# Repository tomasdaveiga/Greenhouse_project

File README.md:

# Greenhouse_project

Project to collect data (temperature, relative humidity, light) from greenhouse for optimised vegetable growth! The long term goal is to have an autonomous and off-the-grid IoT system with a mobile app for data visualisation and monitoring. 

## Phases

The project is split into different phases:
- ~~Phase 1: Design PCBs and cases for the hardware.~~
- Phase 2: Read data from sensors and show it on a display.
- Phase 3: Integrate wireless data transmission and cloud storage followed by an iOS app for data visualisation.
- Phase 4: Add solar pannels for battery charging.

## Hardware

### Sensors:

- Si7020: Temperature and relative humidity sensor
- OPT3001: Visible light sensor
- *Optional Accelerometer: The greenhouse has a window which opens when the temperature is too high. An accelerometer mounted on the window can tell us if the window is open or shut.*

### Microcontroler:
- PSoC-5LP
- Wifi Module for wireless data transmission.
- LCD Display

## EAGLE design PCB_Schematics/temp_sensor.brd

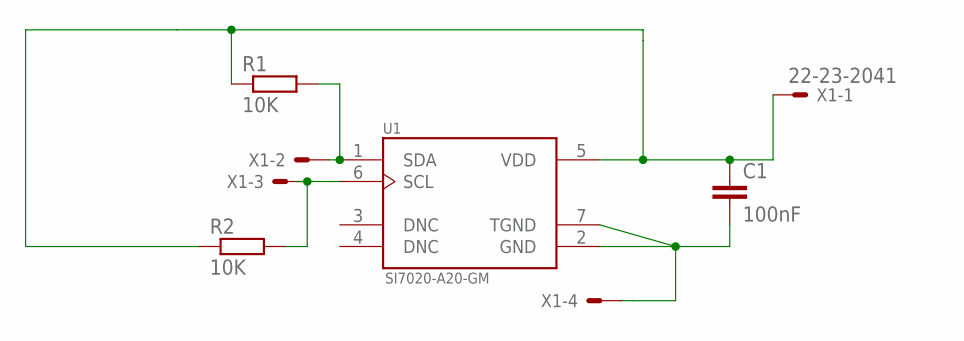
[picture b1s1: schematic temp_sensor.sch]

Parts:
C1: 100nF; C0603
R1, R2: 10K; R0402
U1: SI7020-A20-GM; SON100P300X300X80-7N
X1: 22-23-2041

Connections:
GND: C1.2, U1.2 (GND), U1.7 (TGND), X1.4
SCL: R2.2, U1.6 (SCL), X1.3
SDA: R1.2, U1.1 (SDA), X1.2
VDD: C1.1, R1.1, R2.1, U1.5 (VDD), X1.1

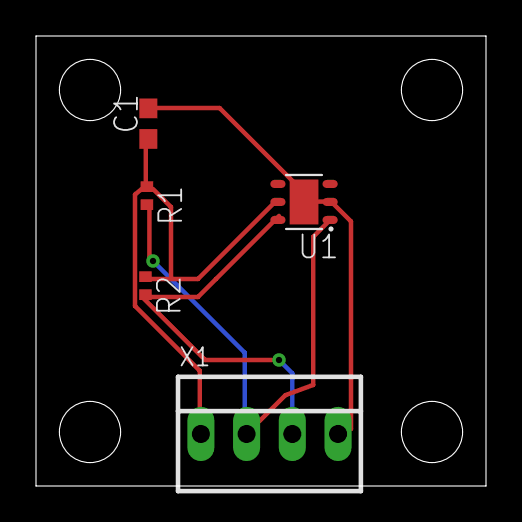
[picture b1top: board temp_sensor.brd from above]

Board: 2 copper layers, 25.0 x 25.0 mm, 5 parts (0 on the bottom side), 4 nets.

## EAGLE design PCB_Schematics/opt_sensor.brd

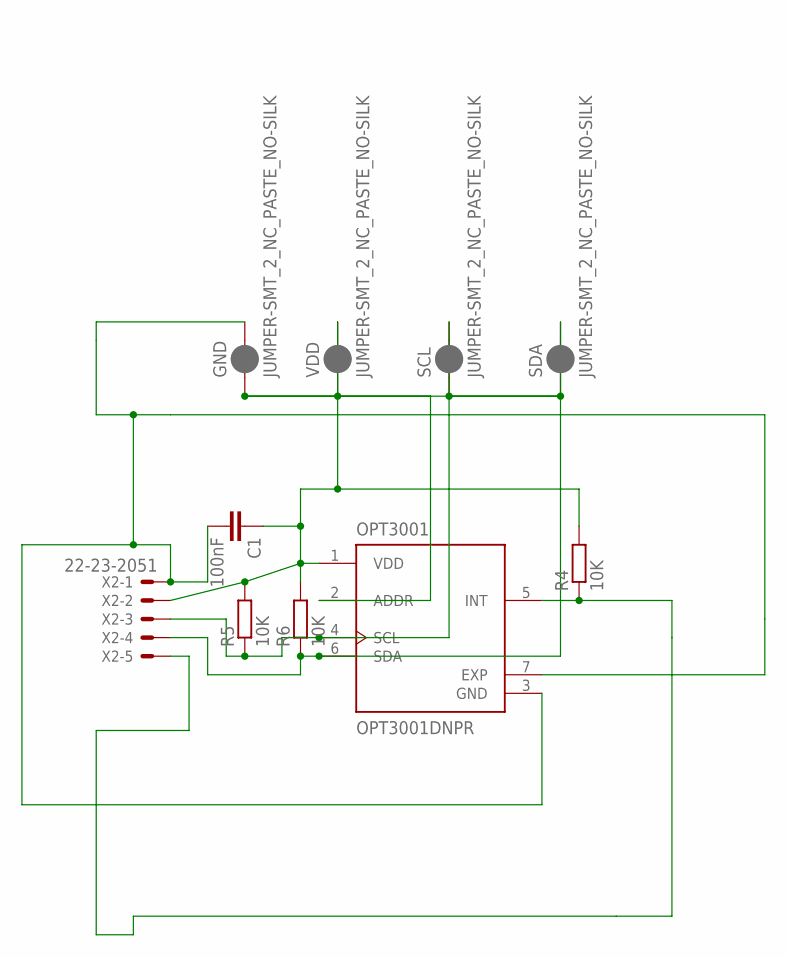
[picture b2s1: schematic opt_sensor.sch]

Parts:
C1: 100nF; C0603
GND: JUMPER-SMT_2_NC_PASTE_NO-SILK; SMT-JUMPER_2_NC_PASTE_NO-SILK
OPT3001: OPT3001DNPR; SON65P200X200X65-7N
R4, R5, R6: 10K; R0402
SCL: JUMPER-SMT_2_NC_PASTE_NO-SILK; SMT-JUMPER_2_NC_PASTE_NO-SILK
SDA: JUMPER-SMT_2_NC_PASTE_NO-SILK; SMT-JUMPER_2_NC_PASTE_NO-SILK
VDD: JUMPER-SMT_2_NC_PASTE_NO-SILK; SMT-JUMPER_2_NC_PASTE_NO-SILK
X2: 22-23-2051

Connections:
ADD: GND.1, OPT3001.2 (ADDR), SCL.1, SDA.1, VDD.1
GND: C1.2, GND.2, OPT3001.3 (GND), OPT3001.7 (EXP), X2.1
INT: OPT3001.5 (INT), R4.1, X2.5
SCL: OPT3001.4 (SCL), R5.1, SCL.2, X2.3
SDA: OPT3001.6 (SDA), R6.1, SDA.2, X2.4
VDD: C1.1, OPT3001.1 (VDD), R4.2, R5.2, R6.2, VDD.2, X2.2

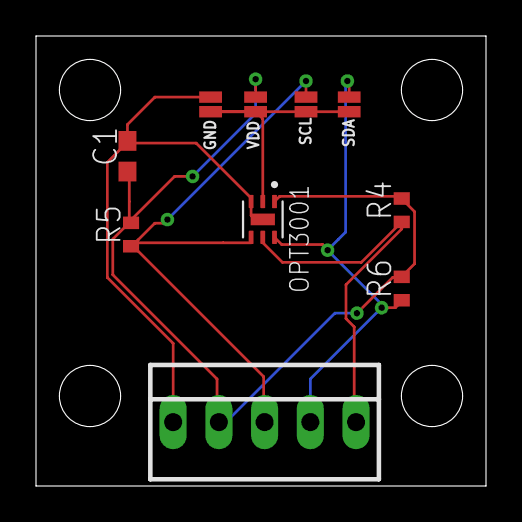
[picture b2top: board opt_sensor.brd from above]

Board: 2 copper layers, 25.0 x 25.0 mm, 10 parts (0 on the bottom side), 6 nets.

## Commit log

2023-04-26 added linux libraries
2023-04-28 added main.c
2023-06-03 Pin Labels
    Added pin labels

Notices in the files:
parts and their libraries:
SparkFun-Jumpers: Licensing: Creative Commons ShareAlike 4.0 International - https://creativecommons.org/licenses/by-sa/4.0
